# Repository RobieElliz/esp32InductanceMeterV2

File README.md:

# Portable ESP32 Inductance Meter

A DIY ESP32-based inductance meter designed to bridge the gap in electronics testing. Developed at the Polytechnic University of the Philippines, this low-cost, high-precision tool is ideal for students, researchers, and hobbyists.

---

## 🔧 Bridging the Gap in Electronics Testing

Accurate inductance measurement is crucial in electronics. Yet, professional meters are often expensive and inaccessible. This project provides an affordable alternative for educational and experimental applications.

---

## 🚀 What It Does

Using LC resonance principles, the device:
- Excites inductors and detects oscillations
- Calculates inductance with high accuracy
- Measures various types of inductors:
  - Toroidal
  - Power
  - Surface-mount (SMD)
  - Air-core  
- Employs dual reference capacitors (100nF & 5µF) for precise mH and µH readings

---

## 🛠 Key Features & Innovations

- **ESP32-powered processing** for real-time calculations  
- **Dual reference capacitors** to optimize accuracy  
- **Capacitive touch controls** for seamless operation  
- **Rechargeable 18650 battery** for true portability  
- **OLED display** for clear, instant readings  
- **Multiple measurement modes:** Single or continuous testing

---

## 📌 Why It Matters

By democratizing access to essential testing equipment, this project empowers the next generation of engineers to innovate and experiment without breaking the bank.

---

## Detailed Components

### 🔧 Dual Reference Capacitors (100nF & 5µF)
- **100nF:** For higher inductance (mH range) with enhanced accuracy  
- **5µF:** Ideal for lower inductance (µH range) ensuring frequency stability

### 🟢 TLV3202 Comparator
- Ultra-high-speed and low-power
- Ensures precise detection of LC oscillations

### ⚡ IP2312 Battery Management IC
- Supports USB Type-C charging (5V, up to 3A)
- Provides overvoltage, undervoltage, and overcurrent protection
- Delivers a stable 3.3V output with buck-boost regulation

### 📟 2.4-inch OLED Display
- Connected via I²C for reduced wiring complexity
- Stacked on the PCB using screws for a compact design
- Displays real-time inductance, frequency, and battery status

---

## Additional Resources

- **OLED Module Purchase:**  
  [Shopee: 2.4" 2.42 inch 128x64 OLED LCD Display Module SSD1309](https://shopee.ph/2.4-2.42-inch-128x64-OLED-LCD-Display-Module-SSD1309-12864-7-Pin-SPI-IIC-I2C-Serial-Interface-for-Arduino-UNO-R3-C51-i.517103615.18774113725?sp_atk=a92714bc-abb0-4431-8565-57df95d88b4a&xptdk=a92714bc-abb0-4431-8565-57df95d88b4a)

---

## License

This project is open source. See the [LICENSE](LICENSE) file for more details.

---

## Made By

This project is made by:  
Johanna Abareta, Ken Louise Aycardo, Katrina Dianne Fernandez, Vince Morales, Robie Elliz Tizon

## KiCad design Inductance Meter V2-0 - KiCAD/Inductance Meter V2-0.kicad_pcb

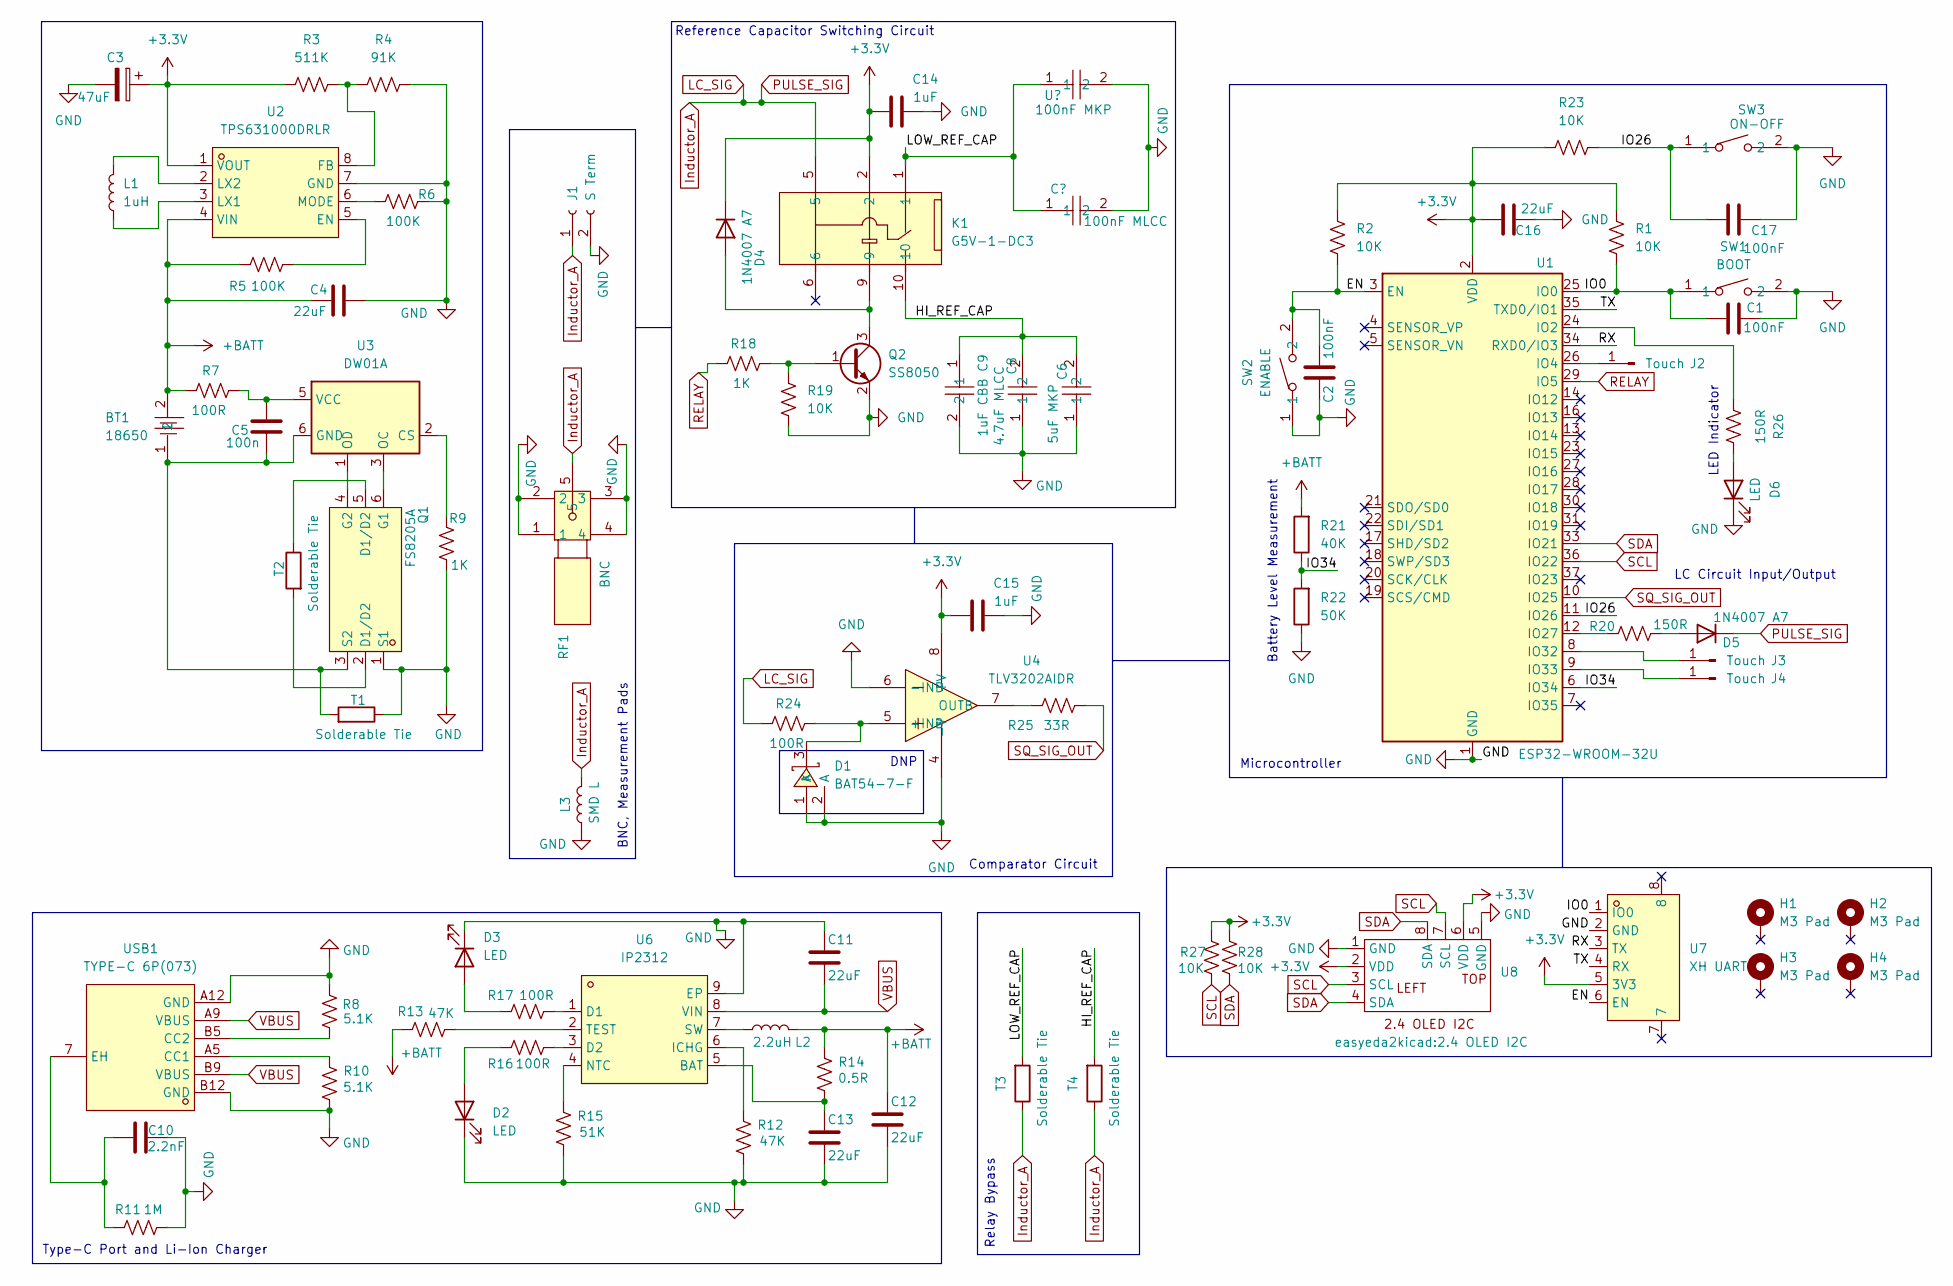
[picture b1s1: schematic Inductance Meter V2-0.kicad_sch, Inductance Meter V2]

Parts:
BT1: 18650; BATTERY-SMD_18650-1S-L77.1-W20.7-1; LCSC Part C2988620
C1, C2, C17: 100nF; C_0805_2012Metric_Pad1.18x1.45mm_HandSolder
C3: 47uF; C_0805_2012Metric_Pad1.18x1.45mm_HandSolder
C4, C11, C12, C13, C16: 22uF; C_0805_2012Metric_Pad1.18x1.45mm_HandSolder
C5: 100n; C_0805_2012Metric
C6: 5uF MKP; CAP-TH_L32.0-W16.0-P27.50-D0.8; LCSC Part C3803313
C8: 4.7uF MLCC; CAP-TH_L5.5-W3.2-P5.00-D0.5; LCSC Part C907942
C9: 1uF CBB; CAP-TH_L26.0-W11.1-P22.50-D1.4; LCSC Part C178465
C10: 2.2nF; C_0805_2012Metric
C14, C15: 1uF; C_0805_2012Metric_Pad1.18x1.45mm_HandSolder
D1: BAT54-7-F; SOT-23-3_L2.9-W1.6-P1.90-LS2.8-BR; LCSC Part C106920
D2, D3, D6: LED; LED_0805_2012Metric_Pad1.15x1.40mm_HandSolder
D4, D5: 1N4007 A7; SOD-123FL_L2.8-W1.8-LS3.7-RD
H1, H2, H3, H4: M3 Pad; MountingHole_3.2mm_M3_Pad_Via
J1: S Term; CONN-TH_2P-P2.54_MX128-2.54-GN01-02P-CU-Y-A
J2, J3, J4: Touch; Touch_Pad_ESP
K1: G5V-1-DC3; RELAY-TH_G5V-1; LCSC Part C397232
L1: 1uH; L_1008_2520Metric
L2: 2.2uH; IND-SMD_L7.1-W6.6; LCSC Part C2847481
L3: SMD L; IND-SMD_L7.1-W6.6; LCSC Part C2847481
Q1: FS8205A; SOT-23-6_L2.9-W1.6-P0.95-LS2.8-BR; LCSC Part C2830320
Q2: SS8050; SOT-23
R1, R2, R19, R23, R27, R28: 10K; R_0805_2012Metric_Pad1.20x1.40mm_HandSolder
R3: 511K; R_0805_2012Metric_Pad1.20x1.40mm_HandSolder
R4: 91K; R_0805_2012Metric_Pad1.20x1.40mm_HandSolder
R5, R6: 100K; R_0805_2012Metric_Pad1.20x1.40mm_HandSolder
R7, R16, R17, R24: 100R; R_0805_2012Metric_Pad1.20x1.40mm_HandSolder
R8, R10: 5.1K; R_0805_2012Metric_Pad1.20x1.40mm_HandSolder
R9, R18: 1K; R_0805_2012Metric_Pad1.20x1.40mm_HandSolder
R11: 1M; R_0805_2012Metric_Pad1.20x1.40mm_HandSolder
R12, R13: 47K; R_0805_2012Metric_Pad1.20x1.40mm_HandSolder
R14: 0.5R; R_0805_2012Metric_Pad1.20x1.40mm_HandSolder
R15: 51K; R_0805_2012Metric_Pad1.20x1.40mm_HandSolder
R20, R26: 150R; R_0805_2012Metric_Pad1.20x1.40mm_HandSolder
R21: 40K; R_0805_2012Metric
R22: 50K; R_0805_2012Metric
R25: 33R; R_0805_2012Metric_Pad1.20x1.40mm_HandSolder
RF1: BNC; BNC-TH_DOSIN-801-0051; LCSC Part C521210
SW1: BOOT; SW-SMD_L3.9-W3.0-P4.45; LCSC Part C720477
SW2: ENABLE; SW-SMD_L3.9-W3.0-P4.45; LCSC Part C720477
SW3: ON-OFF; SW-SMD_L3.9-W3.0-P4.45; LCSC Part C720477
T1, T2, T3, T4: Solderable Tie; Net-Tie 0805 Based
U1: ESP32-WROOM-32U
U2: TPS631000DRLR; SOT-583-8_L2.1-W1.2-P0.50-LS1.6-BL; LCSC Part C5219190
U3: DW01A; SOT-23-6
U4: TLV3202AIDR; SOIC-8_L4.9-W3.9-P1.27-LS6.0-BL; LCSC Part C129325
U6: IP2312; SOP-8_L4.9-W3.9-P1.27-LS6.0-BL-EP; LCSC Part C605432
U7: XH UART; CONN-SMD_S6B-XH-SM4-TB-LF-SN; LCSC Part C191914
U8: 2.4 OLED I2C
USB1: TYPE-C 6P(073); TYPE-C-SMD_TYPE-C-6P_5; LCSC Part C668623

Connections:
+3.3V: C3.1, C14.2, C15.2, C16.2, D4.1 (K), K1.2, R1.1, R2.1, R3.1, R23.2, R27.1, R28.1, U1.2 (VDD), U2.1 (VOUT), U4.8 (+V), U7.5 (3V3), U8.2 (VDD), U8.6 (VDD)
+BATT: BT1.2, C4.1, C12.2, L2.2, R5.1, R7.1, R13.1, R14.1, R21.2, U2.4 (VIN)
/EN: C2.2, R2.2, SW2.2, U1.3 (EN), U7.6 (EN)
/HI_REF_CAP: C6.2, C8.2, C9.1, K1.10, T4.1
/IO0: C1.1, R1.2, SW1.1, U1.25 (IO0), U7.1 (IO0)
/IO2: R26.1, U1.24 (IO2)
/IO26: C17.1, R23.1, SW3.1, U1.11 (IO26)
/IO34: R21.1, R22.2, U1.6 (IO34)
/LOW_REF_CAP: K1.1, T3.1; also elsewhere on the board
/RX: U1.34 (RXD0/IO3), U7.3 (TX)
/TX: U1.35 (TXD0/IO1), U7.4 (RX)
GND: C1.2, C2.1, C3.2, C4.2, C6.1, C8.1, C9.2, C10.2, C11.2, C12.1, C13.1, C14.1, C15.1, C16.1, C17.2, D1.1 (A), D1.2 (A), D2.1 (K), D3.1 (K), D6.1 (K), J1.2, L3.1, Q1.1 (S1), Q2.2 (E), R4.2, R6.2, R8.2, R9.2, R10.2, R11.2, R12.2, R15.2, R19.1, R22.1, RF1.1, RF1.2, RF1.3, RF1.4, SW1.2, SW2.1, SW3.2, T1.2, U1.1 (GND), U1.15 (GND), U1.38 (GND), U1.39 (GND), U2.7 (GND), U4.4 (-V), U4.6 (-INB), U6.9 (EP), U7.2 (GND), U8.1 (GND), U8.5 (GND), USB1.A12 (GND), USB1.B12 (GND); also elsewhere on the board
Inductor_A: D5.1 (K), J1.1, K1.5, L3.2, R24.1, RF1.5, T3.2, T4.2
unnamed: D1.3 (K), R24.2, U4.5 (+INB)
unnamed: D2.2 (A), R16.1
unnamed: D3.2 (A), R17.1
unnamed: D4.2 (A), K1.9, Q2.3 (C)
unnamed: D5.2 (A), R20.2
unnamed: D6.2 (A), R26.2
unnamed: J2.1, U1.26 (IO4)
unnamed: J3.1, U1.8 (IO32)
unnamed: J4.1, U1.9 (IO33)
unnamed: Q1.2 (D1/D2), T2.1
unnamed: Q1.5 (D1/D2), T2.2
unnamed: Q1.6 (G1), U3.3 (OC)
unnamed: Q1.4 (G2), U3.1 (OD)
unnamed: BT1.1, C5.2, Q1.3 (S2), T1.1, U3.6 (GND)
unnamed: Q2.1 (B), R18.2, R19.2
unnamed: R20.1, U1.12 (IO27)
unnamed: R5.2, U2.5 (EN)
unnamed: R3.2, R4.1, U2.8 (FB)
unnamed: L1.1, U2.3 (LX1)
unnamed: L1.2, U2.2 (LX2)
unnamed: R6.1, U2.6 (MODE)
unnamed: R9.1, U3.2 (CS)
unnamed: C5.1, R7.2, U3.5 (VCC)
unnamed: R25.1, U4.7 (OUTB)
unnamed: C13.2, R14.2, U6.5 (BAT)
unnamed: R17.2, U6.1 (D1)
unnamed: R16.2, U6.3 (D2)
unnamed: R12.1, U6.6 (ICHG)
unnamed: R15.1, U6.4 (NTC)
unnamed: L2.1, U6.7 (SW)
unnamed: R13.2, U6.2 (TEST)
unnamed: R10.1, USB1.A5 (CC1)
unnamed: R8.1, USB1.B5 (CC2)
unnamed: C10.1, R11.1, USB1.7 (EH)
RELAY: R18.1, U1.29 (IO5)
SCL: R27.2, U1.36 (IO22), U8.3 (SCL), U8.7 (SCL)
SDA: R28.2, U1.33 (IO21), U8.4 (SDA), U8.8 (SDA)
SQ_SIG_OUT: R25.2, U1.10 (IO25)
VBUS: C11.1, U6.8 (VIN), USB1.A9 (VBUS), USB1.B9 (VBUS)

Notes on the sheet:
LC Circuit Input/Output
Reference Capacitor Switching Circuit
Battery Level Measurement
BNC, Measurement Pads
Type-C Port and Li-Ion Charger
Microcontroller
Comparator Circuit
Relay Bypass
DNP
LED Indicator

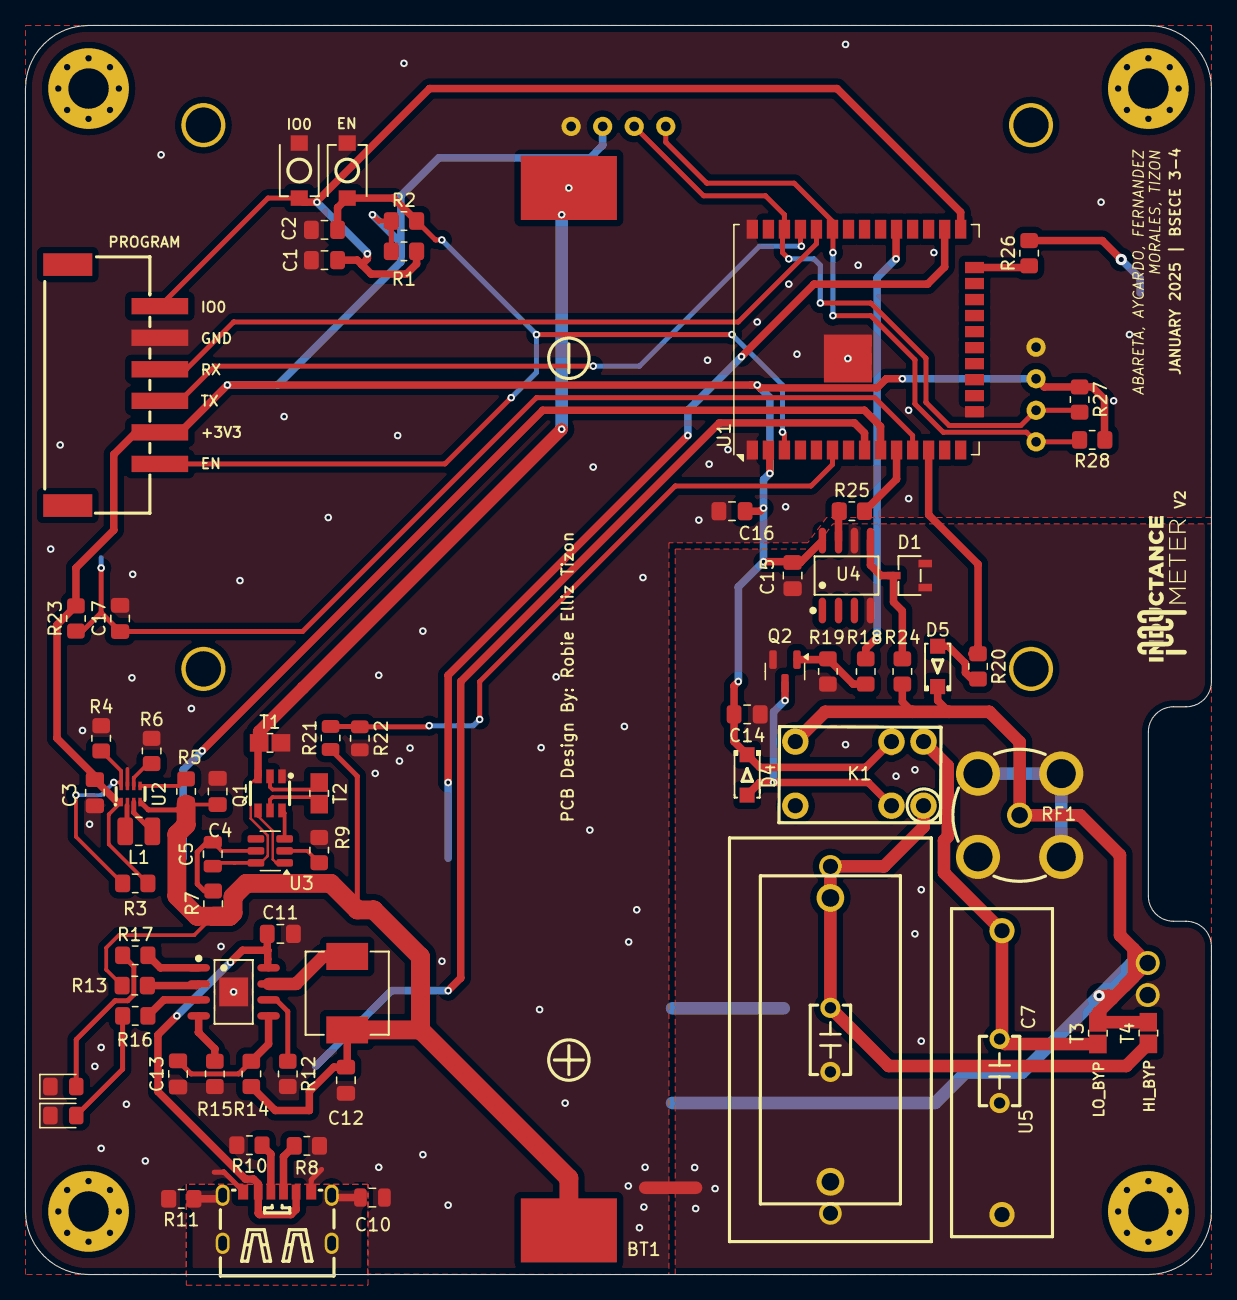
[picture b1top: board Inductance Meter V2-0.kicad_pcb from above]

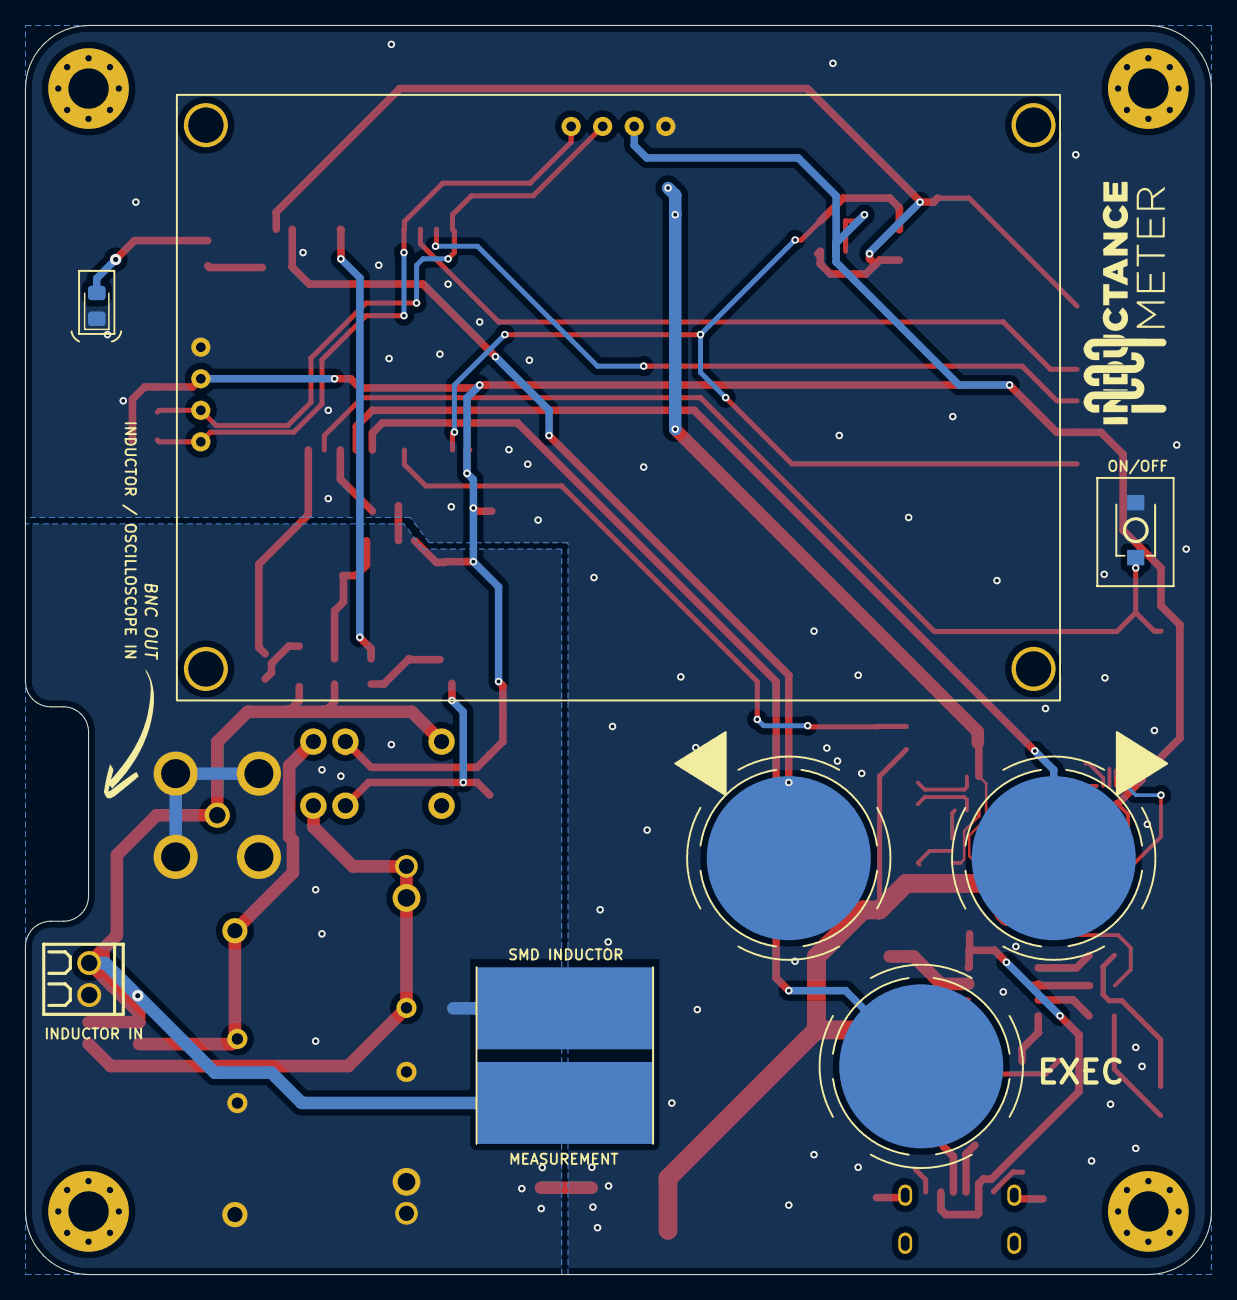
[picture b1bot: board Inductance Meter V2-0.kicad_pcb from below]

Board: 2 copper layers, 94.0 x 99.0 mm, 83 parts (8 on the bottom side), 52 nets.

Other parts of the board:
C7: 100nF MLCC; CAP-TH_L5.5-W3.2-P5.00-D0.5
U5: 100nF MKP; CAP-TH_L26.0-W8.0-P22.50-D0.8

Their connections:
/LOW_REF_CAP: C7.1, U5.1; also elsewhere on the board
GND: C7.2, U5.2; also elsewhere on the board

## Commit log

2025-02-11 First
2025-02-11 photos
